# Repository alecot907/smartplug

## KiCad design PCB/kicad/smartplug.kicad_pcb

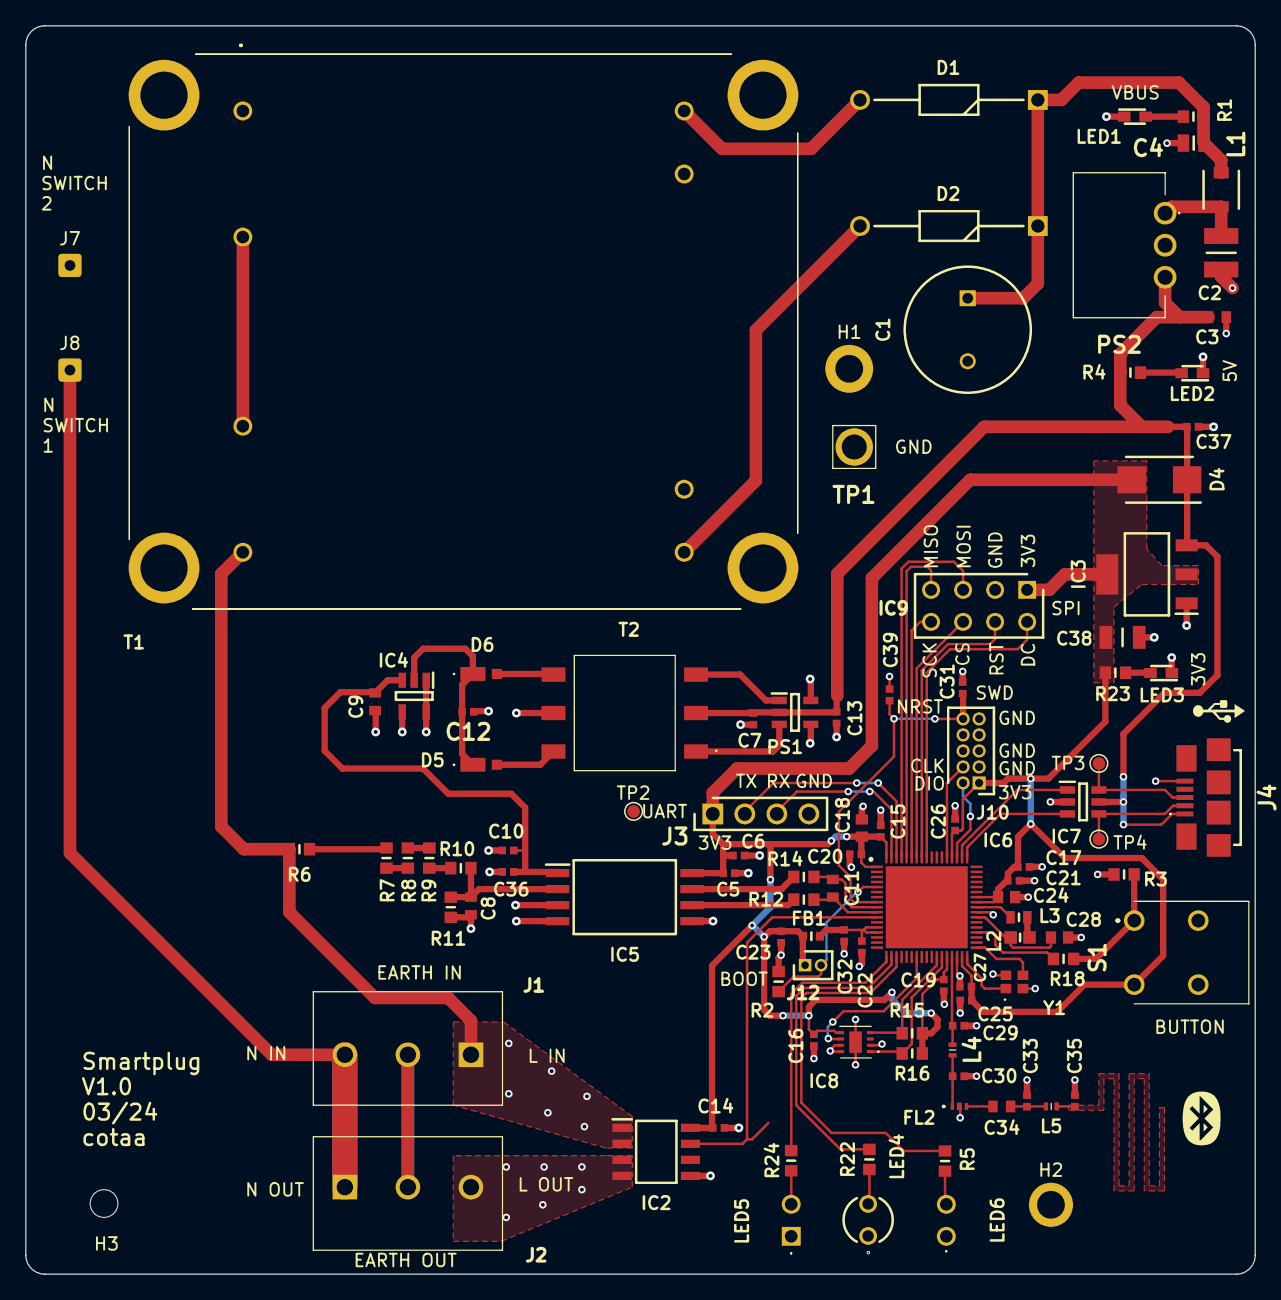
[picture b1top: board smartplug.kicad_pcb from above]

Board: 2 copper layers, 97.5 x 99.0 mm, 105 parts (0 on the bottom side), 70 nets.

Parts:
C1: 470u; CAPPRD500W65D1000H2200
C2: 10u; CAPC3225X270N
C3: 22u; CAPC1608X90N
C4: 4.7u; CAPC2012X135N
C5, C7, C12, C13, C23, C32, C36, C37: 1u; CAPC1005X55N
C6, C10, C14, C15, C16, C17, C19, C20, C21, C22, C25, C26, C31, C39: 0.1u; CAPC1005X55N
C8, C11: 1n; CAPC1608X90N
C9: 10u; CAPC1608X90N
C18, C24, C28: 4.7u; CAPC1608X95N
C27: 100p; CAPC1005X55N
C29: 0.8p; CAPC1005X55N
C30: 0.3p; CAPC1005X55N
C33: n.f.; CAPC1005X55N
C34: 10n; CAPC1608X90N
C35: 1.2p; CAPC1005X55N
C38: 2.2u; CAPC3116X180N
D1, D2: 1N4007RLG; DIOAD1405W86L465D235
D4: S1AB-13-F; DIOM5336X250N
D5, D6: PD3S120L-7; PD3S120L7
FB1: 120R; BLM18EG101TH1D
FL2: LFB182G45CGFD436
H1: MountingHole_Pad; MountingHole_2.2mm_M2_ISO14580_Pad
H2: MountingHole_Pad; MountingHole_2.2mm_M2_ISO7380_Pad
H3: MountingHole; MountingHole_2.2mm_M2_ISO7380
IC2: SOIC127P600X175-8N
IC3: SOT230P700X180-4N
IC4: SOT95P280X145-5N
IC5: SOIC127P1150X280-8N
IC6: QFN40P800X800X100-69N-D
IC7: SOT95P280X145-6N
IC8: SHT30DISB25KS
IC9: 534998-4; RHDR8W76P254X254_2X4_1016X503X673P
J1, J2: 1935174
J3: 826629-4; HDRV4W64P0X254_1X4_1016X254X834P
J4: 10118192-0002LF; 101181920002LF
J7, J8: Conn_01x01; SolderWire-0.25sqmm_1x01_D0.65mm_OD1.7mm
J10: HDRV10W45P127_2X5_635X343X575P
J12: M50-3530242; HDRV2W40P0X127_1X2_254X210X420P
L1: 12u; 1227ASH100MP2
L2: 10uH; INDC1608X95N
L3: 10 nH; LQW18AS10NG0CD
L4: 2.7n; LQG15WH0N7B02D
L5: 3.6n; LQG15WH0N7B02D
LED1, LED2, LED3: GREEN; LEDM168X50N
LED4: GREEN; 151034GS03000
LED5: RED; 151033RS03000
LED6: BLUE; 151034BS03000
PS1: SOT95P280X145-5N
PS2: VXO7805-1000; VXO780121000
R1: 2.2k; RESC1608X55N
R2, R3, R15, R16, R18: 10K; RESC1608X55N
R4: 300R; RESC1608X55N
R5: 47R; RESC1608X55N
R6, R7, R8, R9, R10: 715k; RESC1608X55N
R11: 52.3k; RESC1608X55N
R12, R14: 10R; RESC1608X55N
R22, R23, R24: 120R; RESC1608X55N
S1: 800SP9B5M6RE
T1: FL69
T2: 750313769
TP1: 5023
TP2, TP3, TP4: TestPoint; TestPoint_Pad_D1.0mm
Y1: 32MHZ; NX2016SA32MEXS00ACS06465

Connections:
5V_ISO: C9.2, C10.1, C36.2, IC4.3 (OUT), IC5.1 (VDD1)
+3.3V: C5.2, C6.1, C14.1, C15.1, C16.1, C17.1, C18.2, C19.1, C20.1, C21.1, C23.2, C24.2, C25.1, C26.1, C27.2, C38.2, D4.2, FB1.1, IC2.8 (VS), IC3.2 (OUT_1), IC3.4 (OUT_2), IC5.8 (VDD2), IC6.1 (VBAT), IC6.30 (VDD_1), IC6.33 (VDDRF), IC6.44 (VDDSMPS), IC6.45 (VDD_2), IC6.55 (VDDUSB), IC6.68 (VDD_3), IC8.5 (VDD), IC9.1, J3.1, J10.1, J12.1, R15.2, R16.2, R23.2, S1.3
+3.3VA: C22.1, C32.2, FB1.2, IC6.13 (VREF+), IC6.14 (VDDA)
+5V: C3.2, C7.2, C13.2, C37.2, D4.1, IC3.3 (IN), IC7.5 (VBUS), J4.1 (VCC), PS1.2 (VCC), PS2.3 (+VOUT), R4.2, T2.2 (PRI_2)
/interfaces/FEED: C35.2, L5.2
/interfaces/MATCH_IMP: C33.1, C34.2, L5.1
AN_IIN: IC2.7 (VOUT), IC6.11 (PC2), TP2.1
AN_VIN+: C11.2, IC6.9 (PC0), R14.2
AN_VIN-: C11.1, IC6.10 (PC1), R12.2
BOOT: IC6.5 (PH3-BOOT0), J12.2, R2.2
DISPLAY_DC: IC6.60 (PC12), IC9.2
DISPLAY_RST: IC6.61 (PD0), IC9.4
DISPLAY_SPI_CS: IC6.62 (PD1), IC9.6
DISPLAY_SPI_MISO: IC6.64 (PB4), IC9.7
DISPLAY_SPI_MOSI: IC6.65 (PB5), IC9.5
DISPLAY_SPI_SCK: IC6.63 (PB3), IC9.8
EARTH: J1.2, J2.2
GND: C1.2, C2.1, C3.1, C4.1, C5.1, C6.2, C7.1, C13.1, C14.2, C15.2, C16.2, C17.2, C18.1, C19.2, C20.2, C21.2, C22.2, C23.1, C24.1, C25.2, C26.2, C27.1, C28.1, C29.1, C30.1, C31.2, C32.1, C33.2, C35.1, C37.1, C38.1, C39.2, FL2.2 (GND), H1.1, H2.1, IC2.5 (GND), IC3.1 (GND), IC5.5 (GND2), IC6.32 (VSSRF), IC6.42 (VSSSMPS), IC7.2 (GND), IC8.2 (ADDR), IC8.7 (R), IC8.8 (VSS), IC8.9 (EP), IC9.3, J3.4, J4.5 (GND), J10.3, J10.5, J10.9, LED1.1, LED2.1, LED3.1, LED4.1, LED5.1, LED6.1, PS1.4 (GND_1), PS1.5 (GND_2), PS2.2 (GND), R2.1, R3.1, S1.2, S1.4, T1.6 (SEC2_2), T1.7 (SEC1_1), T1.MH3, T1.MH4, TP1.1, Y1.2 (GND_1), Y1.4 (GND_2)
L: IC2.1 (IN+_1), IC2.2 (IN+_2), J1.1, R6.1, T1.4 (PRI2_2)
L1: IC2.3 (IN-_1), IC2.4 (IN-_2), J2.3
LED_BLUE: IC6.20 (PA5), R5.1
LED_GREEN: IC6.19 (PA4), R22.1
LED_RED: IC6.18 (PA3), R24.1
N: J1.3, J2.1, J8.1
N1: C8.1, C9.1, C10.2, C12.1, C36.1, IC4.1 (GND), IC4.4 (NC_1), IC4.5 (NC_2), IC5.3 (INN), IC5.4 (GND1), J7.1, R11.1, T1.1 (PRI1_1), T2.5 (SEC_2)
NRST: C31.1, C39.1, IC6.8 (NRST), J10.10
unnamed: C30.2, FL2.1 (IN), L4.1
unnamed: C34.1, FL2.3 (OUT)
unnamed: C12.2, D5.1, D6.1, IC4.2 (IN)
unnamed: C8.2, IC5.2 (INP), R10.2, R11.2
unnamed: IC5.6 (OUTN), R12.1
unnamed: IC5.7 (OUTP), R14.1
unnamed: C28.2, IC6.41 (VFBSMPS), L2.2
unnamed: IC6.43 (VLXSMPS), L3.2
unnamed: L2.1, L3.1
unnamed: LED1.2, R1.1
unnamed: LED2.2, R4.1
unnamed: LED3.2, R23.1
unnamed: LED4.2, R22.2
unnamed: LED5.2, R24.2
unnamed: LED6.2, R5.2
unnamed: PS1.1 (D1), T2.3 (PRI_3)
unnamed: PS1.3 (D2), T2.1 (PRI_1)
unnamed: C2.2, L1.2, PS2.1 (+VIN)
unnamed: R6.2, R7.1
unnamed: R7.2, R8.1
unnamed: R8.2, R9.1
unnamed: R9.2, R10.1
unnamed: T1.2 (PRI1_2), T1.3 (PRI2_1)
unnamed: D2.2, T1.5 (SEC2_1)
unnamed: D6.2, T2.4 (SEC_1)
unnamed: D5.2, T2.6 (SEC_3)
OSC_IN: IC6.35 (OSC_IN), Y1.3 (CRY_2)
OSC_OUT: IC6.34 (OSC_OUT), Y1.1 (CRY_1)
RF1: C29.2, IC6.31 (RF1), L4.2
SWCLK: IC6.56 (PA14), J10.4
SWDIO: IC6.54 (PA13), J10.2
SWITCH: IC6.38 (PB0), R18.1
SW_SWITCH: R3.2, R18.2, S1.1
TH_SENS_RST: IC6.24 (PA9), IC8.6 (NRESET)
TH_SENS_SCL: IC6.28 (PB10), IC8.4 (SCL), R15.1
TH_SENS_SDA: IC6.29 (PB11), IC8.1 (SDA), R16.1
UART1_RX: IC6.67 (PB7), J3.3
UART1_TX: IC6.66 (PB6), J3.2
USB_CONN_D+: IC7.6 (I/O1_2), J4.3 (D+), TP3.1
USB_CONN_D-: IC7.4 (I/O2_2), J4.2 (D-), TP4.1
USB_D+: IC6.53 (PA12), IC7.1 (I/O1_1)
USB_D-: IC6.52 (PA11), IC7.3 (I/O2_1)
VBUS: C1.1, C4.2, D1.1, D2.1, L1.1, R1.2
VIN_AC: D1.2, T1.8 (SEC1_2)

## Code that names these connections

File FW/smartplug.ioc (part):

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Mcu.Name=STM32WB55RGVx
Mcu.Package=VFQFPN68
Mcu.UserName=STM32WB55RGVx
PA11.Mode=Device
PA11.Signal=USB_DM
PA12.Mode=Device
PA12.Signal=USB_DP
PA13.Mode=Serial_Wire
PA13.Signal=SYS_JTMS-SWDIO
PA14.Mode=Serial_Wire
PA14.Signal=SYS_JTCK-SWCLK
PA3.Signal=GPIO_Output
PA4.Signal=GPIO_Output
PA5.Signal=GPIO_Output
PA9.Signal=GPIO_Output
PB0.Signal=GPIO_Input
PB10.Mode=I2C
PB10.Signal=I2C3_SCL
PB11.Mode=I2C
PB11.Signal=I2C3_SDA
PB3.Mode=Simplex_Bidirectional_Master
PB3.Signal=SPI1_SCK
PB5.Mode=Simplex_Bidirectional_Master
PB5.Signal=SPI1_MOSI
PB6.Mode=Asynchronous
PB6.Signal=USART1_TX
PB7.Mode=Asynchronous
PB7.Signal=USART1_RX
PC0.Signal=ADCx_IN1
PC1.Signal=ADCx_IN2
PC12.Signal=GPIO_Output
PC2.Signal=ADCx_IN3
PD0.Signal=GPIO_Output
PD1.Signal=GPIO_Output
PH3-BOOT0.GPIOParameters=GPIO_PuPd
PH3-BOOT0.GPIO_PuPd=GPIO_PULLDOWN
PH3-BOOT0.Signal=GPIO_Input
RCC.HSE_VALUE=32000000
RCC.SYSCLKFreq_VALUE=64000000
RCC.SYSCLKSource=RCC_SYSCLKSOURCE_PLLCLK
board=custom

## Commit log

2024-02-02 Added PCB and FW projects
2024-02-02 Moved H3 silk on PCB. Updated manufacturing files.
2024-02-28 PCB 1.0: - Corrected 5V generation - Corrected USB ESD protection - Replaced USB type-C with micro type-B
2024-02-29 Antenna chip replaced with antenna trace on PCB Switch replaced with button Added GND test point Added PD res on Boot pin Added NRST capacitor
2024-02-29 Modified year silk
2024-03-02 Added some test points
